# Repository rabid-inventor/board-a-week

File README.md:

# board-a-week
Board a week project. 

Week 1: PASSIVE BLOCK XOR GATE

Attempting to design a pcb to demonstarate an XOR using Discreet silicon and passive components.
REV1 Design Completed 17/07/18

Week 2: TINYMCU

A Breakout for the Atmel/Microchip AtTiny 4/5/9/10 also suitabe for Microchip PIC10F320/322
REV1 Design Complete 24/07/18

Week 3: INTOKICAD / RABIDCHARLIE

First design using KiCAD Wish me luck. This week I ending up with two designs IntoKiCAD is unfinished it was my first steps in using KiCAD. RabidCHARLE is a complete board ready to produce, containing 12 Charlieplexed LEDs.
RabidCHARLIE REV1 Design Complete 31/07/18

Week 4: BUBBLE WATCH

In Progress!!! , base board finish upper board still work to be done 

Week 5: Lets try a new IC

A breakout board for the brand new BMA400 Accelerometer, designed using limited datasheet information. 

Design Complete 27/08/17

Week 6: Blink A Led

Entry for the Mouser / MacroFAB Blink A Led competition

License / Warranty

These source documents are Licenced as CC-BY feel free to use them just drop me a mention in future projects using them. :)
For further details see LICENCE.md

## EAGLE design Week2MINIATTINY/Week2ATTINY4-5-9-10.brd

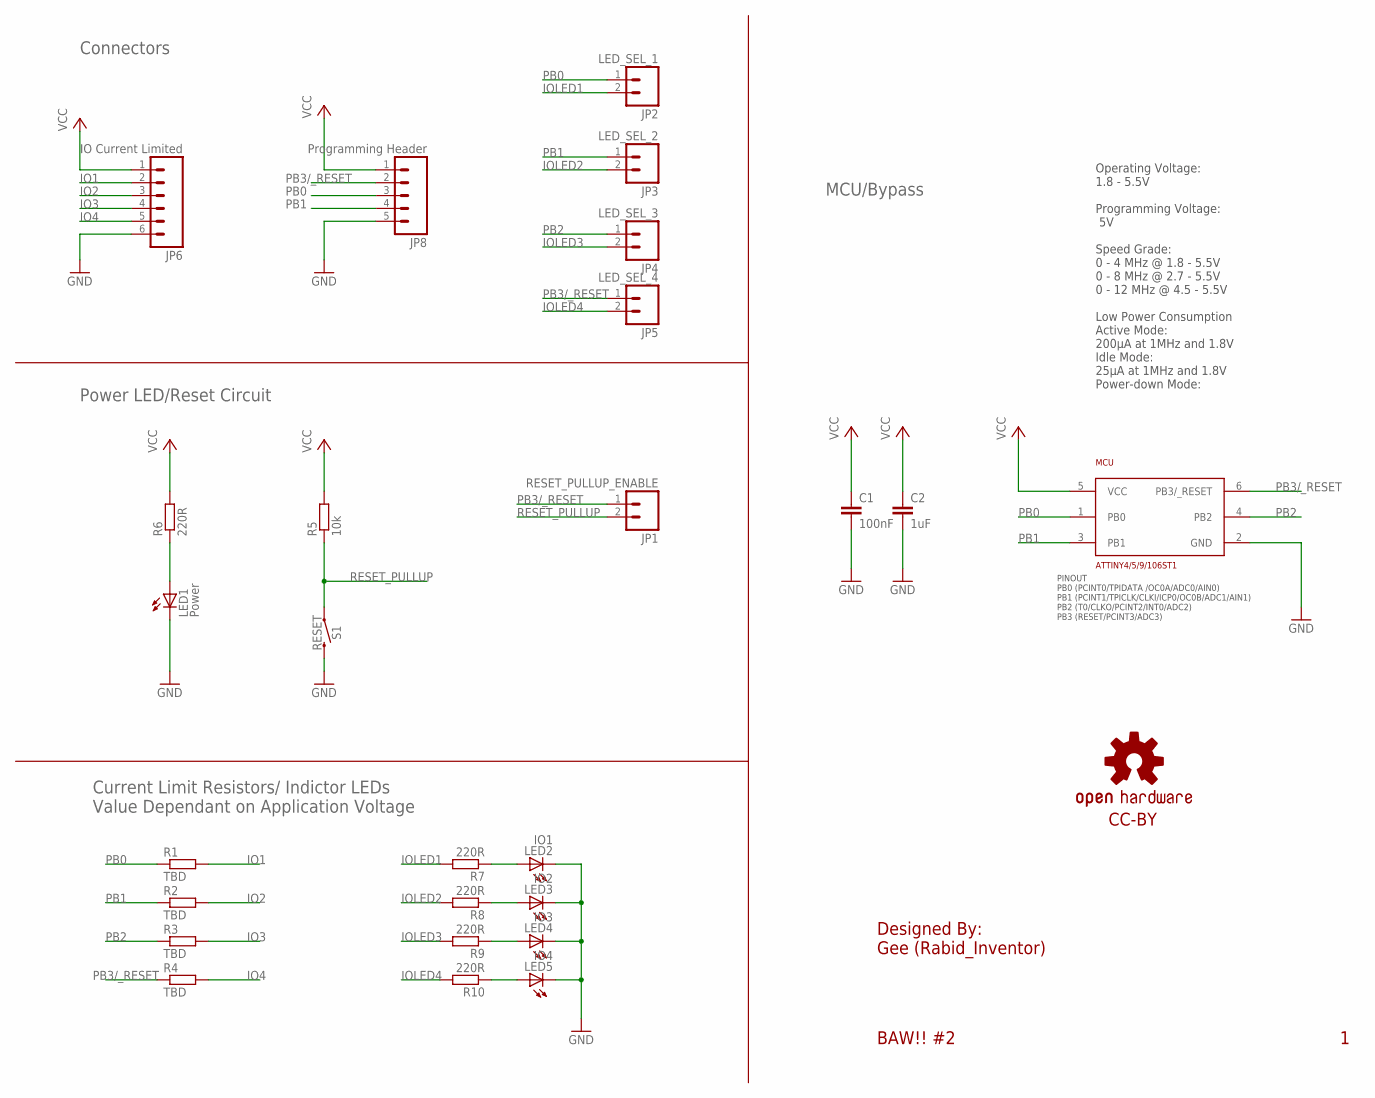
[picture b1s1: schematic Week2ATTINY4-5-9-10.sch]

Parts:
C1: 100nF; C0603K
C2: 1uF; C0603K
JP1: RESET_PULLUP_ENABLE; 1X02_NO_SILK
JP2: LED_SEL_1; 1X02_NO_SILK
JP3: LED_SEL_2; 1X02_NO_SILK
JP4: LED_SEL_3; 1X02_NO_SILK
JP5: LED_SEL_4; 1X02_NO_SILK
JP6: IO Current Limited; 1X06_NO_SILK
JP8: Programming Header; 1X05_NO_SILK
LED1: Power; CHIPLED_0805
LED2: IO1; CHIPLED_0805
LED3: IO2; CHIPLED_0805
LED4: IO3; CHIPLED_0805
LED5: IO4; CHIPLED_0805
LOGO1: OSHW-LOGOMINI; OSHW-LOGO-MINI
MCU: ATTINY4/5/9/106ST1; SOT23-6AVR
R1, R2, R3, R4: TBD; R0603
R5: 10k; R0603
R6, R7, R8, R9, R10: 220R; R0603
S1: RESET; TACTILE_SWITCH_PTH_6.0MM

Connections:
GND: C1.2, C2.2, JP6.6, JP8.5, LED1.C, LED2.C, LED3.C, LED4.C, LED5.C, MCU.2 (GND), S1.3 (2)
IO1: JP6.2, R1.2
IO2: JP6.3, R2.2
IO3: JP6.4, R3.2
IO4: JP6.5, R4.2
IOLED1: JP2.2, R7.2
IOLED2: JP3.2, R8.2
IOLED3: JP4.2, R9.2
IOLED4: JP5.2, R10.2
unnamed: LED1.A, R6.1
unnamed: LED2.A, R7.1
unnamed: LED3.A, R8.1
unnamed: LED4.A, R9.1
unnamed: LED5.A, R10.1
PB0: JP2.1, JP8.3, MCU.1 (PB0), R1.1
PB1: JP3.1, JP8.4, MCU.3 (PB1), R2.1
PB2: JP4.1, MCU.4 (PB2), R3.1
PB3/_RESET: JP1.1, JP5.1, JP8.2, MCU.6 (PB3/_RESET), R4.1
RESET_PULLUP: JP1.2, R5.1, S1.1
VCC: C1.1, C2.1, JP6.1, JP8.1, MCU.5 (VCC), R5.2, R6.2

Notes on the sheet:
Operating Voltage: 1.8 - 5.5V Programming Voltage: 5V Speed Grade: 0 - 4 MHz @ 1.8 - 5.5V 0 - 8 MHz @ 2.7 - 5.5V 0 - 12 MHz @ 4.5 - 5.5V Low Power Consumption Active Mode: 200μA at 1MHz and 1.8V Idle Mode: 25μA at 1MHz and 1.8V Power-down Mode:
MCU/Bypass
Connectors
Power LED/Reset Circuit
Current Limit Resistors/ Indictor LEDs Value Dependant on Application Voltage
Designed By: Gee (Rabid_Inventor)
BAW!! #2
CC-BY

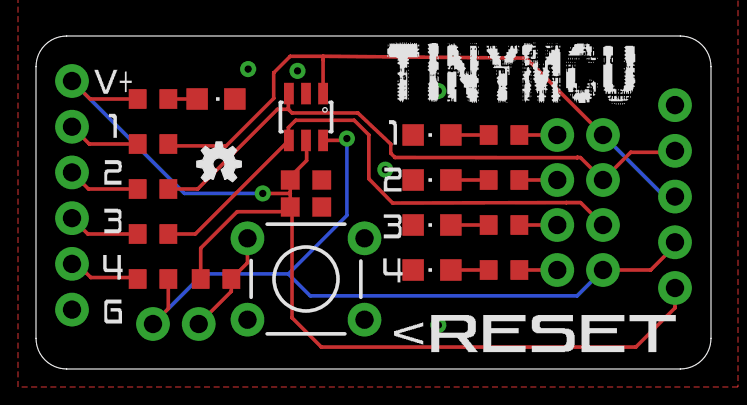
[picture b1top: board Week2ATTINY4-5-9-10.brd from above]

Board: 2 copper layers, 37.5 x 18.5 mm, 27 parts (0 on the bottom side), 20 nets.

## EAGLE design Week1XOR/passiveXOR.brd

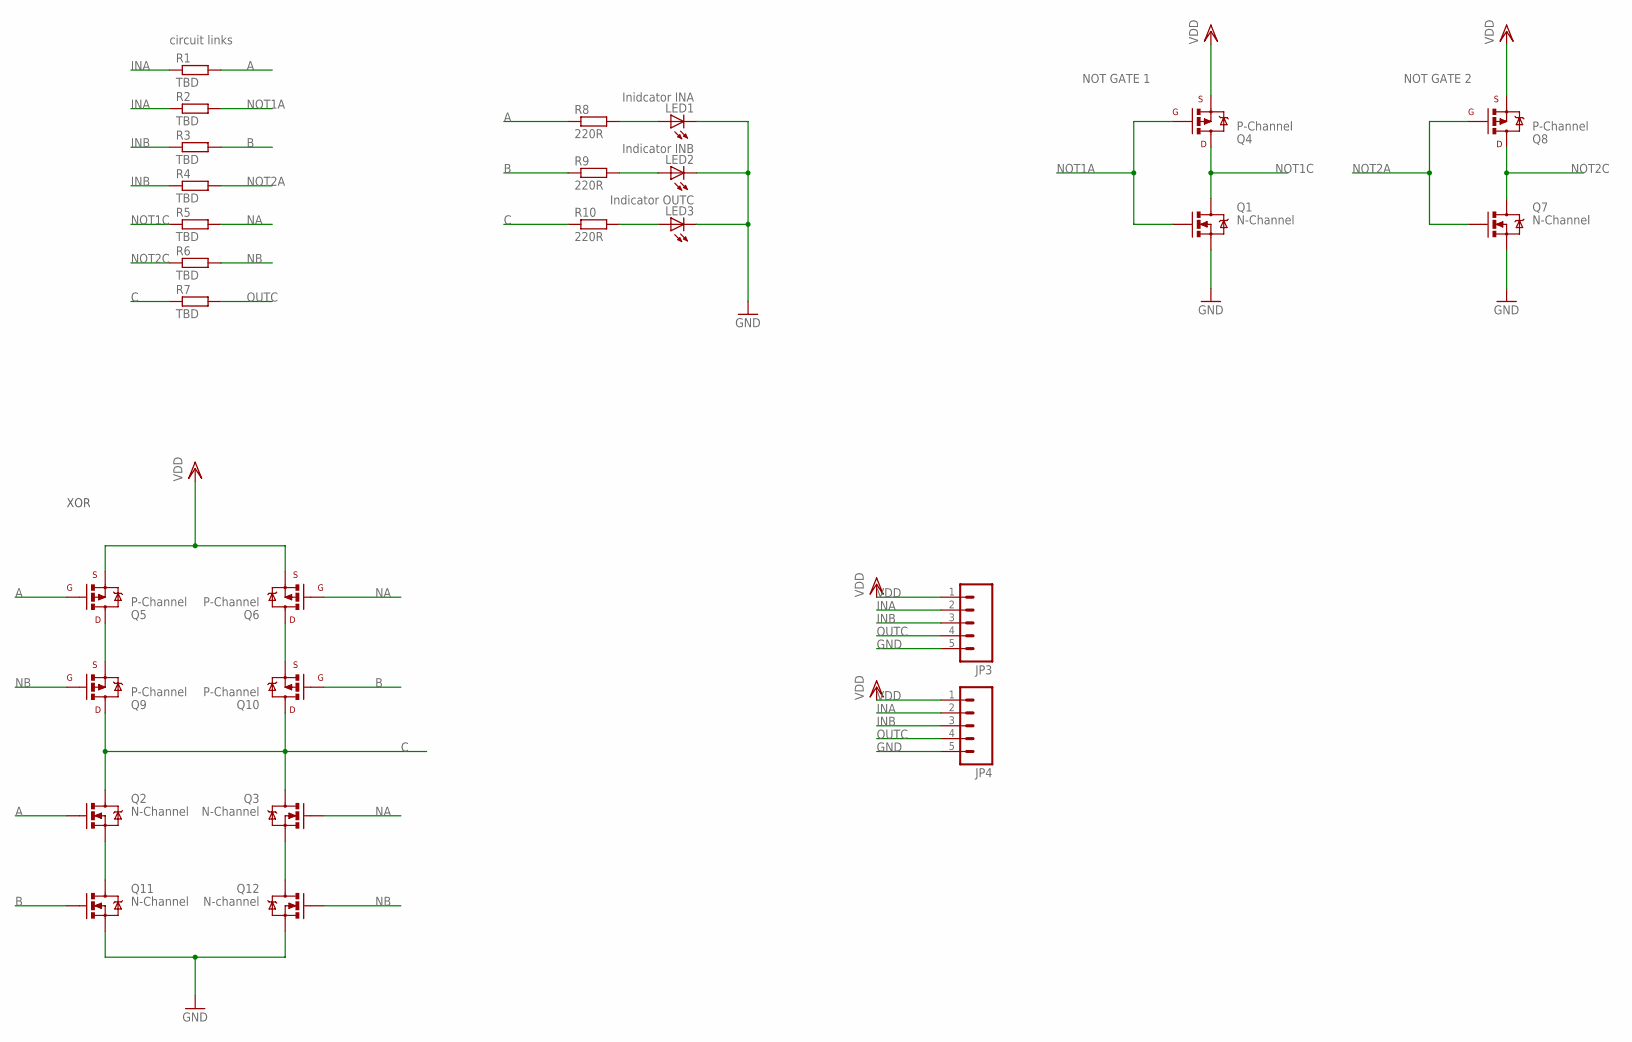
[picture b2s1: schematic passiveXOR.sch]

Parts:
JP3, JP4: M05NO_SILK; 1X05_NO_SILK
LED1: Inidcator INA; CHIPLED_0805
LED2: Indicator INB; CHIPLED_0805
LED3: Indicator OUTC; CHIPLED_0805
Q1, Q2, Q3, Q7, Q11: N-Channel; SOT23
Q4, Q5, Q6, Q8, Q9, Q10: P-Channel; SOT23
Q12: N-channel; SOT23
R1, R2, R3, R4, R5, R6, R7: TBD; R0603
R8, R9, R10: 220R; R0603

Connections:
A: Q2.1 (G), Q5.1 (G), R1.2, R8.1
B: Q10.1 (G), Q11.1 (G), R3.2, R9.1
C: Q2.3 (D), Q3.3 (D), Q9.3 (D), Q10.3 (D), R7.1, R10.1
GND: JP3.5, JP4.5, LED1.C, LED2.C, LED3.C, Q1.2 (S), Q7.2 (S), Q11.2 (S), Q12.2 (S)
INA: JP3.2, JP4.2, R1.1, R2.1
INB: JP3.3, JP4.3, R3.1, R4.1
unnamed: LED1.A, R8.2
unnamed: Q5.3 (D), Q9.2 (S)
unnamed: Q6.3 (D), Q10.2 (S)
unnamed: LED2.A, R9.2
unnamed: LED3.A, R10.2
unnamed: Q2.2 (S), Q11.3 (D)
unnamed: Q3.2 (S), Q12.3 (D)
NA: Q3.1 (G), Q6.1 (G), R5.2
NB: Q9.1 (G), Q12.1 (G), R6.2
NOT1A: Q1.1 (G), Q4.1 (G), R2.2
NOT1C: Q1.3 (D), Q4.3 (D), R5.1
NOT2A: Q7.1 (G), Q8.1 (G), R4.2
NOT2C: Q7.3 (D), Q8.3 (D), R6.1
OUTC: JP3.4, JP4.4, R7.2
VDD: JP3.1, JP4.1, Q4.2 (S), Q5.2 (S), Q6.2 (S), Q8.2 (S)

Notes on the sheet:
XOR
circuit links
NOT GATE 1
NOT GATE 2

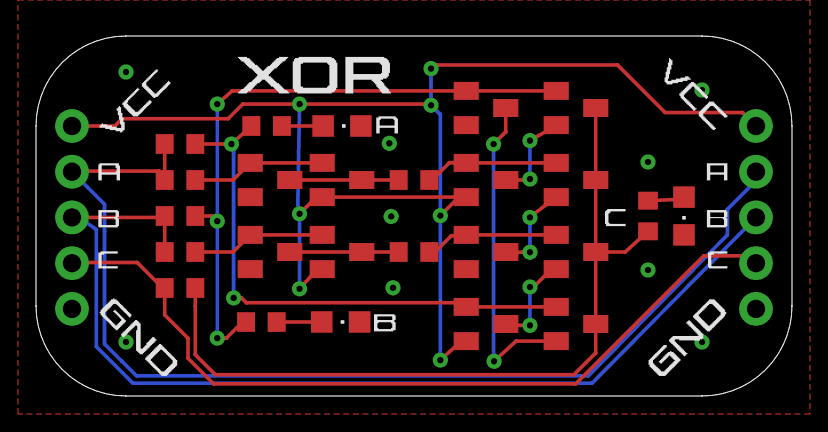
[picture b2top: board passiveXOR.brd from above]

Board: 2 copper layers, 42.0 x 20.0 mm, 27 parts (0 on the bottom side), 21 nets.

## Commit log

2018-07-09 Board schmatic complete
    Finished board schematic. started to layout components.
2018-07-10 First routing Started
2018-07-11 More routing and schmatic fixes
2018-07-12 More routing Tweaking and started to make pretty
2018-07-15 Completed ERC and more desgin tweeks
    Completed ERC making sure i have vaules for parts. Changed header through holds to help with distace to the board edge.
2018-07-16 Routing finished
2018-07-17 Rev1 Finished
    DRC finished silk and artwork added documented fonts used
2018-07-17 added rendered images and updated readme
2018-07-17 Started week2s board
2018-07-18 Started Week 2 ATTINY4/5/9/10
    added parts library to support boards
2018-07-19 schemematic updates
2018-07-20 started processing gerber for week1 more schmatic work for week 2
2018-07-21 Week2 schmatics finished started Week3
2018-07-22 week 2 routing cleaned started silk
2018-07-23 Little bit of playing with the silk for week2(unfinished)
2018-07-24 Week2 Schmatic finished
    Week2 Schmatic finished and tidied up ERC check done values and labels added, added CC-BY Licence details and readme updated
2018-07-24 week 2 more silkwork
2018-07-24 Week2 PCB Complete
2018-07-24 updated readme and renamed week 2 dirctory
2018-07-25 Started Week4
2018-07-28 Restarted Week 3
    Needed to start a new simpler board for week 3 after understanding more about KiCAD.
2018-07-29 Week 3 charlie routing underway
2018-07-30 sorting uncommited changes
2018-07-30 Week3 route finished slik started
2018-07-30 Had forgot to save OPPPs resync
2018-07-30 Week 3 Complete
2018-07-31 Started the flower
2018-07-31 Update to base pattern
2018-08-01 Updated README and tidied the directories
2018-08-01 Started week 4 schmatic
2018-08-03 more bubble watch schematic work
2018-08-05 Schematic done datasheet added
2018-08-05 schematic complete week 4
2018-08-05 Update .gitignore
    Kicad project did no sync removed *.pro
2018-08-05 recommited to update project files for kicad
2018-08-05 Started layout week 4
2018-08-06 update all pro files
2018-08-06 more layout work for Week 4
2018-08-07 more routing work
2018-08-08 new board ideas
2018-08-11 More work on week 4
    Converting display placements to SMT to allow mor room on board.
2018-08-12 more week 4 board work
    full rearangement of pcb an re routing
2018-08-12 repush schmatic
2018-08-13 more week4 routeing reformated dispaly agiain
2018-08-14 end of day commit
2018-08-26 week 5 schematic complete
    added week5 progress
2018-08-26 week 5 routing complete
    silk and artwork still required
2018-08-27 tidying up older projects
2018-08-27 moreschematic work
2018-08-27 finished board updated readme
2018-08-28 Started Week 6
    Started week 6 for Mousers Blink An LED
2018-08-29 Added gerbers to week 5
2018-08-29 End of day sync
2018-09-16 started schematic work on week 7
2018-09-16 trying to make component choices work
2018-09-18 more work on flower
2018-09-24 started on give me power
2018-09-26 more work on week 7
2018-09-27 flower updates
2018-09-28 give me power update
2018-10-08 Finish layout Give Me Power
2018-10-08 updated project file
2018-10-09 started M0GO
2018-10-09 More schematic work
2018-10-12 Added Lora Thing schmatic and almost finished board
2018-10-14 syncing work from lora thing
2018-10-14 loraThing routing complete artwork started
2018-10-14 Resyn forgot to save first (again)
2018-10-15 loar thing artworkupdated
2018-10-16 lorathing artwork
2018-10-16 lora thing complete
2018-10-16 re arrange directories
2018-10-17 m0go SCHEMATIC WORK
2018-11-01 finish schmatic m0go
2018-11-01 resync
2018-11-10 lib updates
2018-11-29 started routing
2018-12-06 board work m0go
2018-12-10 mogo routing finished
2018-12-11 routign finisted on M0GO
2018-12-13 grebers created mogo finished
2018-12-13 revisiting the bubble watch from week 4
2019-01-02 Bubblewathc reborn routing finished
2019-01-02 end of day push
2019-01-03 Started HDMY hdmi swticher
2019-01-03 almost completed HDMY schematic
2019-01-06 completed schmatic working on layout for HDMY
2019-02-26 added rain Randon Air Indication Node
2019-02-27 Rain silks and gerber done
2019-02-28 differential traces done on hdmy
2019-03-01 end of week push
2019-03-18 started first pcbmode project

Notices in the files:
parts and their libraries:
SparkFun-Connectors: Licensing: Creative Commons ShareAlike 4.0 International - https://creativecommons.org/licenses/by-sa/4.0
